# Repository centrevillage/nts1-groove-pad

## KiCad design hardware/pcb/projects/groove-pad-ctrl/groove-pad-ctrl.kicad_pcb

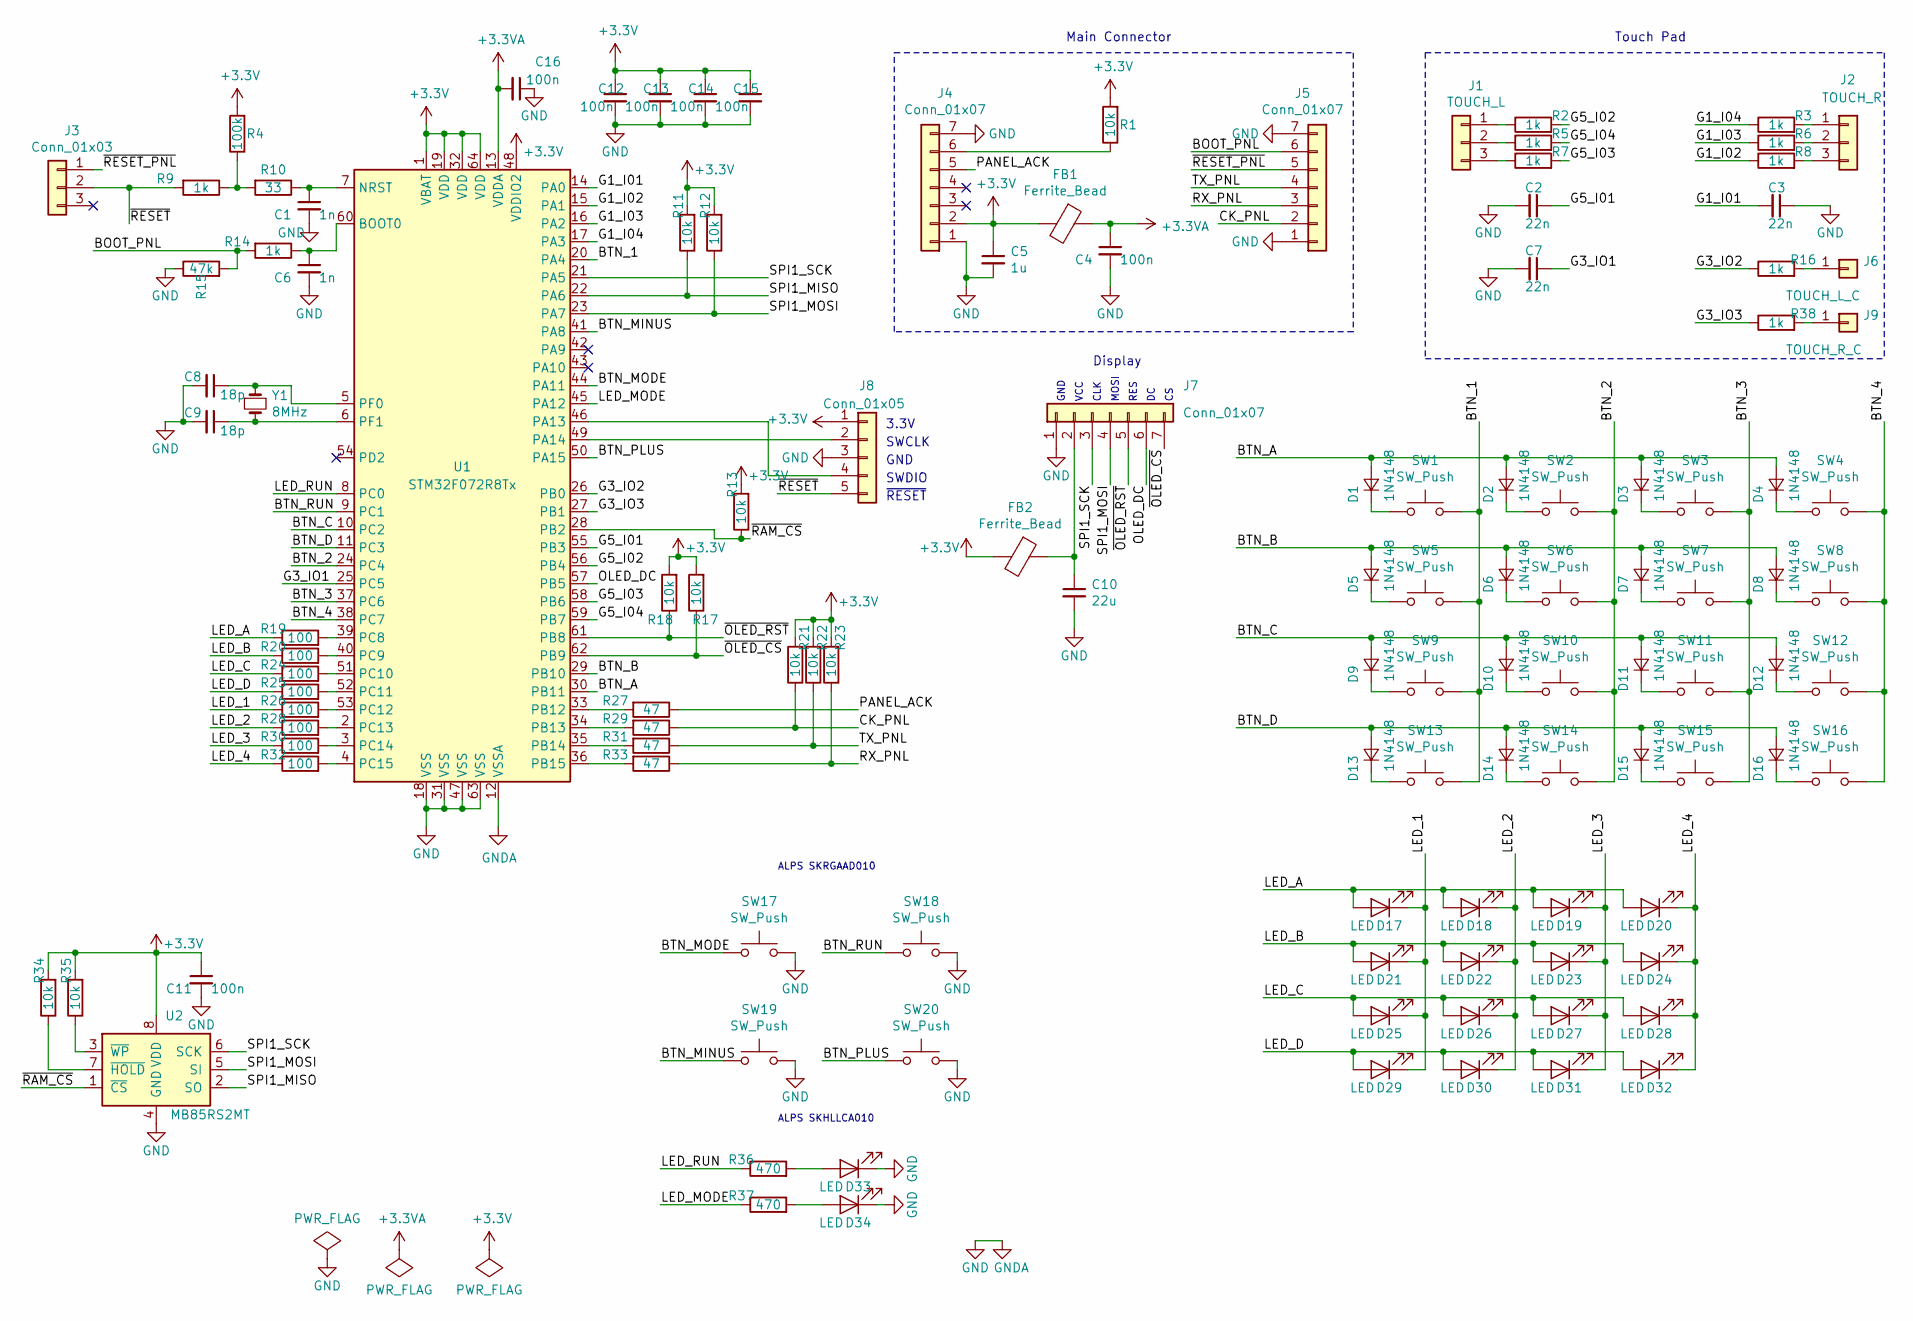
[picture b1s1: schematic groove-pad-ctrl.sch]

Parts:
C1, C6: 1n; C_0603_1608Metric
C2, C3, C7: 22n; C_0603_1608Metric
C4, C11, C12, C13, C14, C15, C16: 100n; C_0603_1608Metric
C5: 1u; C_1206_3216Metric
C8, C9: 18p; C_0603_1608Metric
C10: 22u; C_1206_3216Metric
D1, D2, D3, D4, D5, D6, D7, D8, D9, D10, D11, D12, D13, D14, D15, D16: 1N4148; SOD-123_mod2
D17, D18, D19, D20, D21, D22, D23, D24, D25, D26, D27, D28, D29, D30, D31, D32, D33, D34: LED; LED_0603_1608Metric_Castellated
FB1, FB2: Ferrite_Bead; R_0805_2012Metric
J1: TOUCH_L; CassettePad
J2: TOUCH_R; CassettePad
J3: Conn_01x03; PinHeader_1x03_P2.54mm_Vertical
J4, J5, J7: Conn_01x07; PinHeader_1x07_P2.54mm_Vertical
J6: TOUCH_L_C; PAD_CENTER
J8: Conn_01x05; PinHeader_1x05_P2.54mm_Vertical
J9: TOUCH_R_C; PAD_CENTER
R1, R11, R12, R13, R17, R18, R21, R22, R23, R34, R35: 10k; R_0603_1608Metric
R2, R3, R5, R6, R7, R8, R9, R14, R16, R38: 1k; R_0603_1608Metric
R4: 100k; R_0603_1608Metric
R10: 33; R_0603_1608Metric
R15: 47k; R_0603_1608Metric
R19, R20, R24, R25, R26, R28, R30, R32: 100; R_0603_1608Metric
R27, R29, R31, R33: 47; R_0603_1608Metric
R36, R37: 470; R_0603_1608Metric
SW1, SW2, SW3, SW4, SW5, SW6, SW7, SW8, SW9, SW10, SW11, SW12, SW13, SW14, SW15, SW16, SW17, SW18: SW_Push; SW_Tactile_SKRH
SW19, SW20: SW_Push; SW_Tactile_SPST_Angled_ALPS_SKHLL
U1: STM32F072R8Tx; LQFP-64_10x10mm_P0.5mm
U2: MB85RS2MT
Y1: 8MHz; Crystal_SMD_Abracon_ABM3-2pin_5.0x3.2mm_hand

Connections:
+3.3VA: C4.1, C16.2, FB1.1, U1.13 (VDDA)
+3V3: C5.1, C11.1, C12.1, C13.1, C14.1, C15.1, FB1.2, FB2.2, J4.2, J8.1, R1.2, R4.2, R11.2, R12.2, R13.2, R17.2, R18.2, R21.2, R22.2, R23.2, R34.2, R35.2, U1.1 (VBAT), U1.19 (VDD), U1.32 (VDD), U1.48 (VDDIO2), U1.64 (VDD), U2.8 (VDD)
/BOOT_PNL: J5.6, R14.2, R15.2
/BTN_1: SW1.2, SW5.2, SW9.2, SW13.2, U1.20 (PA4)
/BTN_2: SW2.2, SW6.2, SW10.2, SW14.2, U1.24 (PC4)
/BTN_3: SW3.2, SW7.2, SW11.2, SW15.2, U1.37 (PC6)
/BTN_4: SW4.2, SW8.2, SW12.2, SW16.2, U1.38 (PC7)
/BTN_A: D1.2 (A), D2.2 (A), D3.2 (A), D4.2 (A), U1.30 (PB11)
/BTN_B: D5.2 (A), D6.2 (A), D7.2 (A), D8.2 (A), U1.29 (PB10)
/BTN_C: D9.2 (A), D10.2 (A), D11.2 (A), D12.2 (A), U1.10 (PC2)
/BTN_D: D13.2 (A), D14.2 (A), D15.2 (A), D16.2 (A), U1.11 (PC3)
/BTN_MINUS: SW19.1, U1.41 (PA8)
/BTN_MODE: SW17.1, U1.44 (PA11)
/BTN_PLUS: SW20.1, U1.50 (PA15)
/BTN_RUN: SW18.1, U1.9 (PC1)
/CK_PNL: J5.2, R21.1, R29.1
/G1_I01: C3.2, U1.14 (PA0)
/G1_I02: R8.1, U1.15 (PA1)
/G1_I03: R6.1, U1.16 (PA2)
/G1_I04: R3.1, U1.17 (PA3)
/G3_IO1: C7.1, U1.25 (PC5)
/G3_IO2: R16.1, U1.26 (PB0)
/G3_IO3: R38.1, U1.27 (PB1)
/G5_I01: C2.1, U1.55 (PB3)
/G5_I02: R2.2, U1.56 (PB4)
/G5_I03: R7.2, U1.58 (PB6)
/G5_I04: R5.2, U1.59 (PB7)
/LED_1: D17.1 (K), D21.1 (K), D25.1 (K), D29.1 (K), R26.1
/LED_2: D18.1 (K), D22.1 (K), D26.1 (K), D30.1 (K), R28.1
/LED_3: D19.1 (K), D23.1 (K), D27.1 (K), D31.1 (K), R30.1
/LED_4: D20.1 (K), D24.1 (K), D28.1 (K), D32.1 (K), R32.1
/LED_A: D17.2 (A), D18.2 (A), D19.2 (A), D20.2 (A), R19.1
/LED_B: D21.2 (A), D22.2 (A), D23.2 (A), D24.2 (A), R20.1
/LED_C: D25.2 (A), D26.2 (A), D27.2 (A), D28.2 (A), R24.1
/LED_D: D29.2 (A), D30.2 (A), D31.2 (A), D32.2 (A), R25.1
/LED_MODE: R37.1, U1.45 (PA12)
/LED_RUN: R36.1, U1.8 (PC0)
/OLED_DC: J7.6, U1.57 (PB5)
/PANEL_ACK: J4.5, R27.1
/RX_PNL: J5.3, R23.1, R33.1
/SPI1_MISO: R11.1, U1.22 (PA6), U2.2 (SO)
/SPI1_MOSI: J7.4, R12.1, U1.23 (PA7), U2.5 (SI)
/SPI1_SCK: J7.3, U1.21 (PA5), U2.6 (SCK)
/TX_PNL: J5.4, R22.1, R31.1
/~OLED_CS: J7.7, R17.1, U1.62 (PB9)
/~OLED_RST: J7.5, R18.1, U1.61 (PB8)
/~RAM_CS: R13.1, U1.28 (PB2), U2.1 (~CS)
/~RESET: J3.2, J8.5, R9.2
/~RESET_PNL: J3.1, J5.5
GND: C1.2, C2.2, C3.1, C4.2, C5.2, C6.2, C7.2, C8.2, C9.2, C10.2, C11.2, C12.2, C13.2, C14.2, C15.2, C16.1, D33.1 (K), D34.1 (K), J4.1, J4.7, J5.1, J5.7, J7.1, J8.3, R15.1, SW17.2, SW18.2, SW19.2, SW20.2, U1.12 (VSSA), U1.18 (VSS), U1.31 (VSS), U1.47 (VSS), U1.63 (VSS), U2.4 (GND)
unnamed: C1.1, R10.1, U1.7 (NRST)
unnamed: C6.1, R14.1, U1.60 (BOOT0)
unnamed: C8.1, U1.5 (PF0), Y1.1
unnamed: C9.1, U1.6 (PF1), Y1.2
unnamed: C10.1, FB2.1, J7.2
unnamed: D1.1 (K), SW1.1
unnamed: D2.1 (K), SW2.1
unnamed: D3.1 (K), SW3.1
unnamed: D4.1 (K), SW4.1
unnamed: D5.1 (K), SW5.1
unnamed: D6.1 (K), SW6.1
unnamed: D7.1 (K), SW7.1
unnamed: D8.1 (K), SW8.1
unnamed: D9.1 (K), SW9.1
unnamed: D10.1 (K), SW10.1
unnamed: D11.1 (K), SW11.1
unnamed: D12.1 (K), SW12.1
unnamed: D13.1 (K), SW13.1
unnamed: D14.1 (K), SW14.1
unnamed: D15.1 (K), SW15.1
unnamed: D16.1 (K), SW16.1
unnamed: D33.2 (A), R36.2
unnamed: D34.2 (A), R37.2
unnamed: J1.1, R2.1
unnamed: J1.2, R5.1
unnamed: J1.3, R7.1
unnamed: J2.1, R3.2
unnamed: J2.2, R6.2
unnamed: J2.3, R8.2
unnamed: J4.6, R1.1
unnamed: J6.1, R16.2
unnamed: J8.2, U1.49 (PA14)
unnamed: J8.4, U1.46 (PA13)
unnamed: J9.1, R38.2
unnamed: R4.1, R9.1, R10.2
unnamed: R19.2, U1.39 (PC8)
unnamed: R20.2, U1.40 (PC9)
unnamed: R24.2, U1.51 (PC10)
unnamed: R25.2, U1.52 (PC11)
unnamed: R26.2, U1.53 (PC12)
unnamed: R27.2, U1.33 (PB12)
unnamed: R28.2, U1.2 (PC13)
unnamed: R29.2, U1.34 (PB13)
unnamed: R30.2, U1.3 (PC14)
unnamed: R31.2, U1.35 (PB14)
unnamed: R32.2, U1.4 (PC15)
unnamed: R33.2, U1.36 (PB15)
unnamed: R34.1, U2.7 (~HOLD)
unnamed: R35.1, U2.3 (~WP)

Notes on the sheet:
Main Connector
SWCLK
3.3V
SWDIO
GND
Touch Pad
Display
VCC
CLK
MOSI
RES
~RESET
ALPS SKHLLCA010
ALPS SKRGAAD010

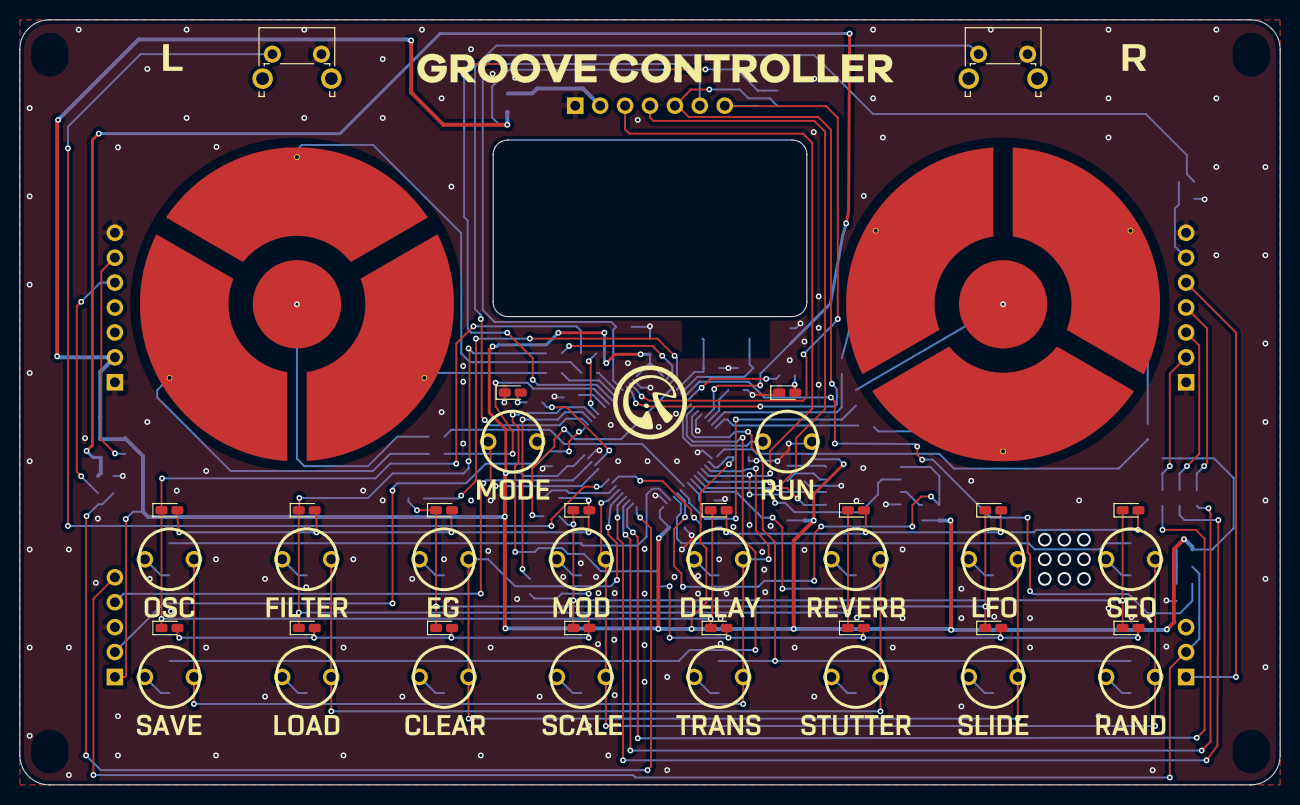
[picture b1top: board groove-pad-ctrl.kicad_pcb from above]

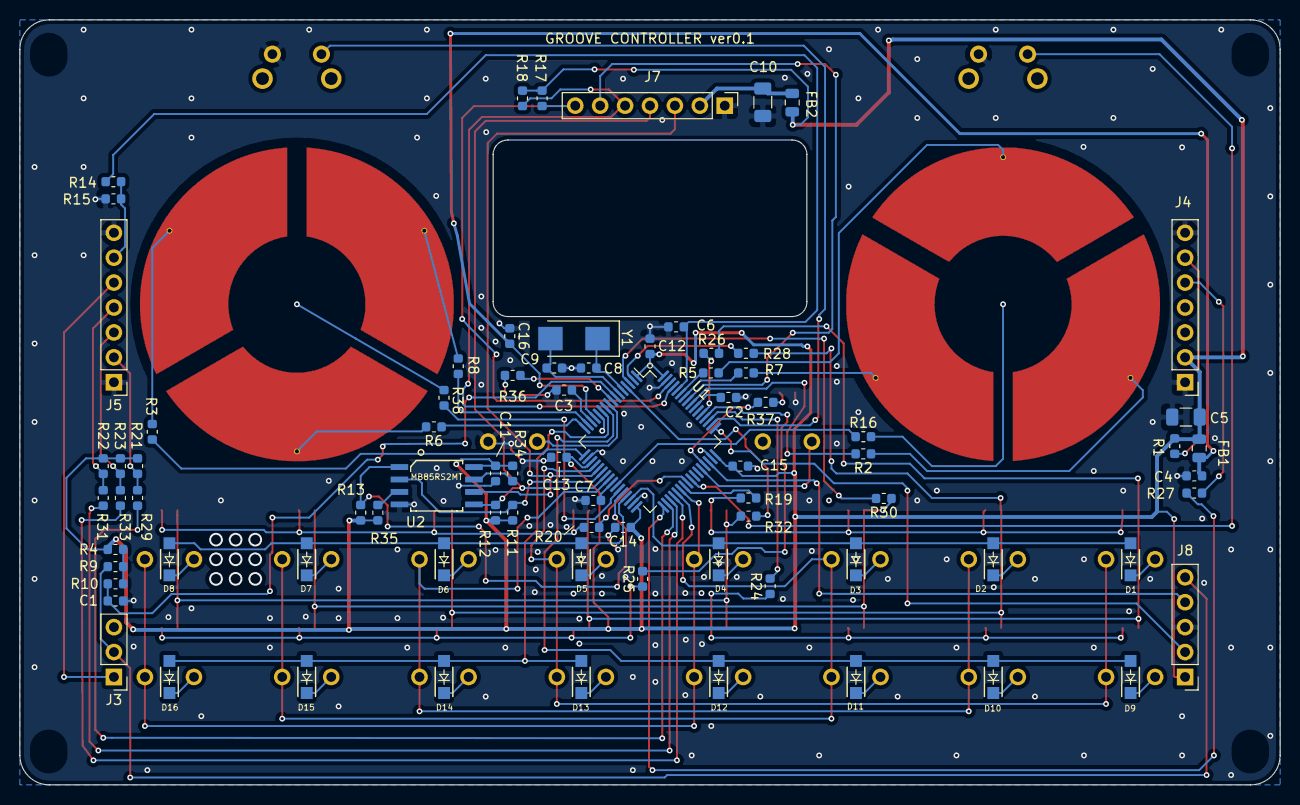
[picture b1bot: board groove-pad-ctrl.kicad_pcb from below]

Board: 2 copper layers, 128.5 x 78.0 mm, 122 parts (80 on the bottom side), 99 nets.

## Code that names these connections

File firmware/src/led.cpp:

#include "main.h"
#include "led.h"

#include <igb_stm32/periph/gpio.hpp>
#include <igb_sdk/ui/led.hpp>

using namespace igb::stm32;
using namespace igb::sdk;

LedMatrix<GpioPin, 4, 4> led_matrix = {
  .a_pins = {
    GpioPin::newPin(GpioPinType::pc8),
    GpioPin::newPin(GpioPinType::pc9),
    GpioPin::newPin(GpioPinType::pc10),
    GpioPin::newPin(GpioPinType::pc11)
  },
  .k_pins = {
    GpioPin::newPin(GpioPinType::pc12),
    GpioPin::newPin(GpioPinType::pc13),
    GpioPin::newPin(GpioPinType::pc14),
    GpioPin::newPin(GpioPinType::pc15)
  }
};

//auto led_a_pin = GpioPin::newPin(GpioPinType::pc8);
//auto led_b_pin = GpioPin::newPin(GpioPinType::pc9);
//auto led_c_pin = GpioPin::newPin(GpioPinType::pc10);
//auto led_d_pin = GpioPin::newPin(GpioPinType::pc11);
//auto led_1_pin = GpioPin::newPin(GpioPinType::pc12);
//auto led_2_pin = GpioPin::newPin(GpioPinType::pc13);
//auto led_3_pin = GpioPin::newPin(GpioPinType::pc14);
//auto led_4_pin = GpioPin::newPin(GpioPinType::pc15);
auto led_run_pin = GpioPin::newPin(GpioPinType::pc0);
auto led_mode_pin = GpioPin::newPin(GpioPinType::pa12);

__IO uint32_t led_bits = 0;

void led_setup() {
  for (auto& pin : led_matrix.a_pins) {
    pin.initOutput(GpioOutputMode::pushpull, GpioSpeedMode::high);
  }
  for (auto& pin : led_matrix.k_pins) {
    pin.initOutput(GpioOutputMode::pushpull, GpioSpeedMode::high);
  }
  //led_a_pin.initOutput(GpioOutputMode::pushpull, GpioSpeedMode::high);
  //led_b_pin.initOutput(GpioOutputMode::pushpull, GpioSpeedMode::high);
  //led_c_pin.initOutput(GpioOutputMode::pushpull, GpioSpeedMode::high);
  //led_d_pin.initOutput(GpioOutputMode::pushpull, GpioSpeedMode::high);
  //led_1_pin.initOutput(GpioOutputMode::pushpull, GpioSpeedMode::high);
  //led_2_pin.initOutput(GpioOutputMode::pushpull, GpioSpeedMode::high);
  //led_3_pin.initOutput(GpioOutputMode::pushpull, GpioSpeedMode::high);
  //led_4_pin.initOutput(GpioOutputMode::pushpull, GpioSpeedMode::high);
  led_run_pin.initOutput(GpioOutputMode::pushpull, GpioSpeedMode::high);
  led_mode_pin.initOutput(GpioOutputMode::pushpull, GpioSpeedMode::high);
}

//GpioPin led_row_pins[] = {
//  led_a_pin, led_b_pin, led_c_pin, led_d_pin
//};

//GpioPin led_col_pins[] = {
//  led_1_pin, led_2_pin, led_3_pin, led_4_pin
//};

void led_process() {
  led_matrix.process();

  //static uint8_t led_matrix_idx = 0;
  //led_row_pins[(led_matrix_idx+3)%4].low();

  led_mode_pin.write(!!(led_bits & (1UL<<16)));
  led_run_pin.write(!!(led_bits & (1UL<<17)));

  //for (uint8_t i=0;i<4;++i) {
  //  led_col_pins[i].write(!(led_bits & (1UL << (led_matrix_idx*4+i))));
  //}
  //led_row_pins[led_matrix_idx].high();

  //led_matrix_idx = (led_matrix_idx+1) % 4;
}

void led_set_run(uint8_t on) {
  led_set(17, on);
}

void led_set_mode(uint8_t on) {
  led_set(16, on);
}

void led_set(uint8_t index, uint8_t on) {
  if (index < 16) {
    led_matrix.set(index / 4, index % 4, on);
  } else {
    if (on) {
      led_bits |= (1UL<<index);
    } else {
      led_bits &= ~(1UL<<index);
    }
  }
};

void led_clear() {
  led_bits = 0;
  led_matrix.allOff();
}

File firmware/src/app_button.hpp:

#ifndef APP_BUTTON_H
#define APP_BUTTON_H

#include <igb_stm32/periph/gpio.hpp>
#include <igb_sdk/ui/button.hpp>
#include <functional>
#include <tuple>

// 危険は承知の上・・・
using namespace igb::stm32;
using namespace igb::sdk;

enum class AppBtnID : uint8_t {
  OSC = 0, PARAM, FILTER, EG, MOD, DELAY, REVERB, ARP,
  SAVE, LOAD, CLEAR, GLOBAL, SCALE, TRANS, STUTTER, LFO,
  SEQ, RUN, L, R,

  SIZE
};

struct AppButtons {
  // こう書けたらいいのに！
  //using namespace igb_stm32;
  //using namespace igb_sdk;

  GpioPort port_a { GpioType::gpioa };
  GpioPort port_b { GpioType::gpiob };
  GpioPort port_c { GpioType::gpioc };

  ButtonSingle<GpioPin> seq_btn { GpioPin::newPin(GpioPinType::pa11) };
  ButtonSingle<GpioPin> run_btn { GpioPin::newPin(GpioPinType::pc1) };
  ButtonSingle<GpioPin> l_btn   { GpioPin::newPin(GpioPinType::pa8) };
  ButtonSingle<GpioPin> r_btn   { GpioPin::newPin(GpioPinType::pa15) };

  ButtonMatrix<GpioPin, 4, GpioPin, 4> btn_matrix {
    .in_pins = {
      GpioPin::newPin(GpioPinType::pa4),
      GpioPin::newPin(GpioPinType::pc4),
      GpioPin::newPin(GpioPinType::pc6),
      GpioPin::newPin(GpioPinType::pc7)
    },
    .out_pins = {
      GpioPin::newPin(GpioPinType::pb11),
      GpioPin::newPin(GpioPinType::pb10),
      GpioPin::newPin(GpioPinType::pc2),
      GpioPin::newPin(GpioPinType::pc3)
    }
  };

  uint32_t state_bits = 0;
  std::function<void(AppBtnID, bool)> on_change;

  void init() {
    port_a.enable();
    port_b.enable();
    port_c.enable();

    seq_btn.pin.initInput(GpioPullMode::up, GpioSpeedMode::high);
    run_btn.pin.initInput(GpioPullMode::up, GpioSpeedMode::high);
    l_btn.pin.initInput(GpioPullMode::up, GpioSpeedMode::high);
    r_btn.pin.initInput(GpioPullMode::up, GpioSpeedMode::high);

    for (const auto& in_pin : btn_matrix.in_pins) {
      in_pin.initInput(GpioPullMode::no, GpioSpeedMode::high);
    }
    for (const auto& out_pin : btn_matrix.out_pins) {
      out_pin.initOutput(GpioOutputMode::pushpull, GpioSpeedMode::high);
    }

    btn_matrix.init();
  }

  inline bool _isOn4Matrix(AppBtnID btn_id) {
    std::tuple<uint8_t, uint8_t> in_out_pin_idx {0, 0};

    switch (btn_id) {
      case AppBtnID::OSC:
        in_out_pin_idx = {0, 0}; break;
      case AppBtnID::PARAM:
        in_out_pin_idx = {1, 0}; break;
      case AppBtnID::FILTER:
        in_out_pin_idx = {2, 0}; break;
      case AppBtnID::EG:
        in_out_pin_idx = {3, 0}; break;
      case AppBtnID::MOD:
        in_out_pin_idx = {0, 1}; break;
      case AppBtnID::DELAY:
        in_out_pin_idx = {1, 1}; break;
      case AppBtnID::REVERB:
        in_out_pin_idx = {2, 1}; break;
      case AppBtnID::ARP:
        in_out_pin_idx = {3, 1}; break;
      case AppBtnID::SAVE:
        in_out_pin_idx = {0, 2}; break;
      case AppBtnID::LOAD:
        in_out_pin_idx = {1, 2}; break;
      case AppBtnID::CLEAR:
        in_out_pin_idx = {2, 2}; break;
      case AppBtnID::GLOBAL:
        in_out_pin_idx = {3, 2}; break;
      case AppBtnID::SCALE:
        in_out_pin_idx = {0, 3}; break;
      case AppBtnID::TRANS:
        in_out_pin_idx = {1, 3}; break;
      case AppBtnID::STUTTER:
        in_out_pin_idx = {2, 3}; break;
      case AppBtnID::LFO:
        in_out_pin_idx = {3, 3}; break;
      default:
        break;
    }
    return btn_matrix.isOn(std::get<0>(in_out_pin_idx), std::get<1>(in_out_pin_idx));
  }

  // TODO: ボタンと対応するインデックスの関連づけ、もっとシンプルに定義できる様にしたい
  bool isOn(AppBtnID btn_id) {
    bool on = false;

    switch (btn_id) {
      case AppBtnID::OSC:
      case AppBtnID::PARAM:
      case AppBtnID::FILTER:
      case AppBtnID::EG:
      case AppBtnID::MOD:
      case AppBtnID::DELAY:
      case AppBtnID::REVERB:
      case AppBtnID::ARP:
      case AppBtnID::SAVE:
      case AppBtnID::LOAD:
      case AppBtnID::CLEAR:
      case AppBtnID::GLOBAL:
      case AppBtnID::SCALE:
      case AppBtnID::TRANS:
      case AppBtnID::STUTTER:
      case AppBtnID::LFO:
        on = _isOn4Matrix(btn_id);
        break;
      case AppBtnID::SEQ:
        on = seq_btn.isOn(); break;
      case AppBtnID::RUN:
        on = run_btn.isOn(); break;
      case AppBtnID::L:
        on = l_btn.isOn(); break;
      case AppBtnID::R:
        on = r_btn.isOn(); break;
      default:
        break;
    }

    return on;
  }

  void process() {
    seq_btn.process();
    run_btn.process();
    l_btn.process();
    r_btn.process();
    btn_matrix.process();
    uint32_t new_bits = 0;
    for (uint8_t i = 0; i < static_cast<uint8_t>(AppBtnID::SIZE); ++i) {
      if (isOn(static_cast<AppBtnID>(i))) {
        new_bits |= (uint32_t)1 << i;
      }
    }
    if (state_bits != new_bits) {
      if (on_change) {
        uint32_t diff_bits = state_bits ^ new_bits;
        state_bits = new_bits;
        for (uint8_t i = 0; i < static_cast<uint8_t>(AppBtnID::SIZE); ++i) {
          if (diff_bits & ((uint32_t)1 << i)) {
            on_change(static_cast<AppBtnID>(i), !!(new_bits & ((uint32_t)1 << i)));
          }
        }
      }
    }
  }
};

#endif /* APP_BUTTON_H */

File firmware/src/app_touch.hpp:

#ifndef N1GP_APP_TOUCH_H
#define N1GP_APP_TOUCH_H

#include "debug.h"
#include <igb_sdk/util/text.h>
#include <igb_stm32/periph/tsc.hpp>
#include <igb_sdk/ui/touch.hpp>
#include <igb_util/cast.hpp>

using namespace igb;
using namespace igb::stm32;
using namespace igb::sdk;

enum class AppTouchPadID : uint8_t {
  L = 0,
  R,
};

struct AppTouch {
  Tsc tsc;
  std::function<void(AppTouchPadID, int16_t)> on_change;
  std::function<void(uint8_t)> on_acquisition_end;

  TouchRot3DialWithCenter<Tsc::Channel> l_pad {
    .channels = {tsc.newChannel(TscChannel::g5i4), tsc.newChannel(TscChannel::g5i3), tsc.newChannel(TscChannel::g5i2)},
    .center_channel = tsc.newChannel(TscChannel::g3i2),
    .steps = 16,
    .steps_on_center = 1
  };

  TouchRot3DialWithCenter<Tsc::Channel> r_pad {
    .channels = {tsc.newChannel(TscChannel::g1i4), tsc.newChannel(TscChannel::g1i3), tsc.newChannel(TscChannel::g1i2)},
    .center_channel = tsc.newChannel(TscChannel::g3i3),
    .steps = 16,
    .steps_on_center = 1
  };

  inline void resetDefaultSteps() {
    l_pad.steps = 16;
    r_pad.steps = 16;
    l_pad.steps_on_center = 1;
    r_pad.steps_on_center = 1;
  }

  inline void setSteps(int16_t l_steps, int16_t r_steps, int16_t l_steps_on_center=1, int16_t r_steps_on_center=1) {
    l_pad.steps = l_steps;
    r_pad.steps = r_steps;
    l_pad.steps_on_center = l_steps_on_center;
    r_pad.steps_on_center = r_steps_on_center;
  }

  inline uint8_t touch_bits_from(uint32_t bits) {
    return (!!(bits & (1UL << as<uint8_t>(TscChannel::g5i2))) << 2) | 
      (!!(bits & (1UL << as<uint8_t>(TscChannel::g5i3))) << 1) |
      (!!(bits & (1UL << as<uint8_t>(TscChannel::g5i4))) << 0) |
      (!!(bits & (1UL << as<uint8_t>(TscChannel::g1i2))) << 5) | 
      (!!(bits & (1UL << as<uint8_t>(TscChannel::g1i3))) << 4) |
      (!!(bits & (1UL << as<uint8_t>(TscChannel::g1i4))) << 3) |
      (!!(bits & (1UL << as<uint8_t>(TscChannel::g3i2))) << 6) |
      (!!(bits & (1UL << as<uint8_t>(TscChannel::g3i3))) << 7);
  }

  inline static bool is_left_bit(uint8_t bits) {
    return bits & (0b01000111);
  }

  inline static bool is_right_bit(uint8_t bits) {
    return bits & (0b10111000);
  }

  void init() {
    tsc.initDefault(
      // R Pad
      TscPinConf { TscChannel::g1i1, GpioPinType::pa0, TscIoType::samplingCap },
      TscPinConf { TscChannel::g1i2, GpioPinType::pa1, TscIoType::input },
      TscPinConf { TscChannel::g1i3, GpioPinType::pa2, TscIoType::input },
      TscPinConf { TscChannel::g1i4, GpioPinType::pa3, TscIoType::input },
      // L Pad
      TscPinConf { TscChannel::g5i1, GpioPinType::pb3, TscIoType::samplingCap },
      TscPinConf { TscChannel::g5i2, GpioPinType::pb4, TscIoType::input },
      TscPinConf { TscChannel::g5i3, GpioPinType::pb6, TscIoType::input },
      TscPinConf { TscChannel::g5i4, GpioPinType::pb7, TscIoType::input },
      // center pad
      TscPinConf { TscChannel::g3i1, GpioPinType::pc5, TscIoType::samplingCap },
      TscPinConf { TscChannel::g3i2, GpioPinType::pb0, TscIoType::input },
      TscPinConf { TscChannel::g3i3, GpioPinType::pb1, TscIoType::input }
    );
    tsc.setThreshold(TscChannel::g1i2, 1000);
    tsc.setThreshold(TscChannel::g1i3, 1000);
    tsc.setThreshold(TscChannel::g1i4, 1000);
    tsc.setThreshold(TscChannel::g5i2, 1000);
    tsc.setThreshold(TscChannel::g5i3, 1000);
    tsc.setThreshold(TscChannel::g5i4, 1000);
    tsc.setThreshold(TscChannel::g3i2, 1000);
    tsc.setThreshold(TscChannel::g3i3, 1000);

    tsc.on_acquisition_end = [this](uint32_t bits) {
      l_pad.process();
      r_pad.process();
      auto l_val = l_pad.value();
      if (l_val.has_value()) {
        on_change(AppTouchPadID::L, l_val.value());
      }
      auto r_val = r_pad.value();
      if (r_val.has_value()) {
        on_change(AppTouchPadID::R, r_val.value());
      }
      if (on_acquisition_end) {
        on_acquisition_end(touch_bits_from(bits));
      }
    };
  }

  void process() {
    tsc.process();
  }
};

extern AppTouch app_touch;

#endif /* N1GP_APP_TOUCH_H */

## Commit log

2020-02-21 ver 0.1
2020-03-11 add firmware dir
2020-03-11 change MCU
2020-04-11 OLEDが動かない・・・・
2020-04-14 色々やったが相変わらずOLED動かん
2020-04-30 spi通信処理を見直したら画面が映るようになったが座標がへん？
2020-04-30 OLEDの実際のwidthは128pxじゃなくて130pxぽい？
2020-05-03 add tsc function
2020-05-08 OLEDへのビットマップ描画テスト
2020-05-11 TSCの対応
2020-05-15 ボタン操作とLEDの点灯制御
2020-05-17 refactoring timer
2020-05-18 add build dir
2020-05-18 add Makefile (but not working...)
2020-05-19 add state
2020-05-20 add nts1_defs
2020-05-24 fix nts1_defs
2020-05-26 NTS1本体からのパラメータ読み込み
2020-05-27 bugfix
2020-05-27 run nts1_idle in loop
2020-05-27 fix param name display
2020-06-01 refactoring spi
2020-06-01 タッチパッドによる値の変更
2020-06-02 fix touch response
2020-06-02 タッチ入力の不具合修正
2020-06-04 FRAMへのプリセット保存処理
2020-06-04 input_refresh on load
2020-06-06 一時保存処理
2020-08-05 シーケンス入力処理(途中)
2020-08-12 シーケンス機能の抽象化と簡易実装
2020-08-12 ライブラリコードをlib以下に移動
2020-08-12 余分なusing宣言を削除
2020-08-13 add igb_stm32
2020-08-14 GPIO周りの抽象化とライブラリ化（途中）
2020-08-14 bugfix for AppButtons
2020-08-16 bugfix for ButtonMatrix
2020-08-16 remove button.h/c
2020-08-20 add svd file parser
2020-08-21 fix ADCInfo and svd parser
2020-08-22 add peripheral bus info
2020-08-23 add enum class for each peripheral
2020-08-23 ネーミングルールの統一化
2020-08-29 add tim peripheral
2020-09-12 igb_stm32: add spi peripheral
2020-09-12 oled.cをLL非依存に
2020-09-12 ram.c(pp)をLL非依存にし、不要となったファイルを削除
2020-09-12 ledとpresetをLL非依存に
2020-09-12 performance tuning
2020-09-27 add tsc peripheral
2020-09-27 remove unused code
2020-09-29 igb namespace の構造変更
2020-10-04 LL依存箇所を完全削除
2020-10-09 入力処理のモダンC++化
2020-10-11 refactoring
2020-10-11 input周りのコードを分割
2020-10-14 screenのcpp化(途中)
2020-10-14 fix app_screen
2020-10-18 remove unused files
2020-10-26 Timer -> Tim
2020-10-30 add systick lib and remove systick_timer.h/c
2020-11-04 add debug display for touch state
2020-11-04 add touch method for input class
2020-11-15 add soft_timer
2020-11-15 implement sequencer
2020-11-20 add oled_ssd1306 to sdk
2020-11-21 add bitmap font to sdk
2020-11-21 add fram_mb85r_spi to sdk
2020-11-21 add led to sdk
2020-11-22 bugfix: fram lib spi issue
2020-11-22 add draw method to oled lib
2020-11-22 add text lib to sdk
2020-11-22 igb_sdk を外部lib化
2021-06-29 update igb_sdk
